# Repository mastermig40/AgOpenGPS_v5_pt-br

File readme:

Este conteúdo é apenas para colaborar com a comunidade AGopenGPS, agradecimentos ao Brian e sua comunidade...

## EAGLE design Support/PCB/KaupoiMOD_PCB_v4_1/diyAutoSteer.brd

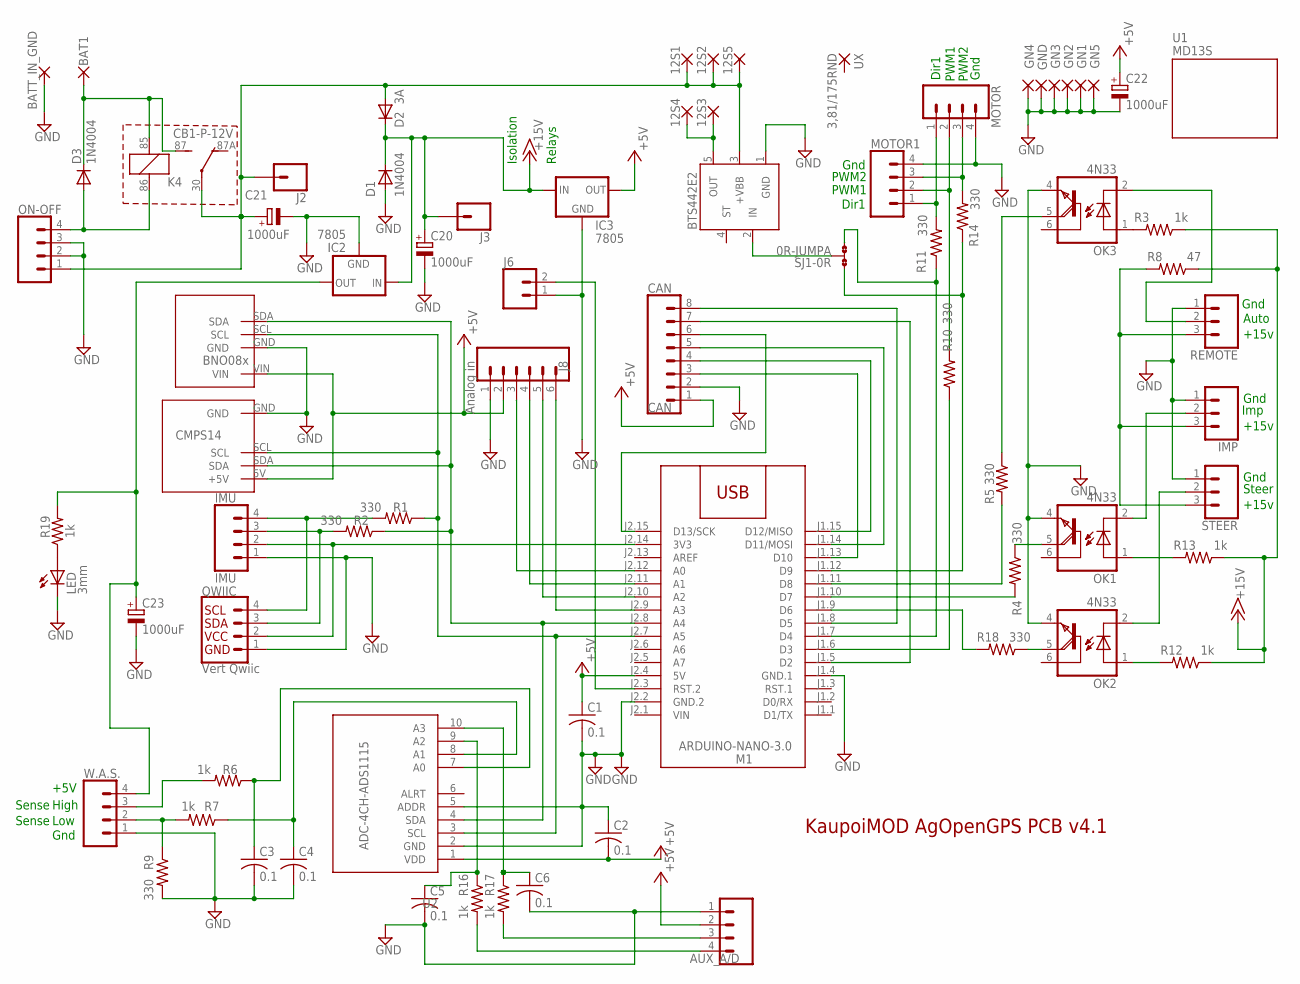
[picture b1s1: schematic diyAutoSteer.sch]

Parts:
12S1, 12S2, 12S3, 12S4, 12S5: 3,81/1,65
AUX_A/D: CONN_04LONGPADS; 1X04_LONGPADS
BAT1: 3,81/1,65
BATT_IN_GND: 3,81/1,65
C1, C2, C3, C4, C5, C6: 0.1; C025-025X050
C20, C21, C22, C23: 1000uF; E5-13
CAN: CAN; 1X08_NO_SILK
D1, D3: 1N4004; DO41-10
D2: 3A; DO27-15
GN1, GN2, GN3, GN4, GN5: 3,81/1,65
GND: 3,81/1,65
IC2, IC3: 7805; 78XXS
IMP: CONN_03LONGPADS; 1X03_LONGPADS
IMU: IMU; 1X04_LONGPADS
J2, J3: CONN_01; 1X01
J6: CONN_02PTH3; 1X02_LONGPADS
J8: Analog in; 1X06_NO_SILK
K4: CB1-P-12V; CB1
LED: 3mm; LED3MM
M1: ARDUINO-NANO-3.0
MOTOR, MOTOR1: CONN_04LONGPADS; 1X04_LONGPADS
OK1, OK2, OK3: 4N33; DIL06
ON-OFF: CONN_04LONGPADS; 1X04_LONGPADS
QWIIC: Vert Qwiic; JST04_1MM_VERT
R1, R2, R4, R5, R9, R10, R11, R14, R18: 330; 0309/12
R3, R6, R7, R12, R13, R16, R17, R19: 1k; 0309/12
R8: 47; 0309/12
REMOTE: CONN_03LONGPADS; 1X03_LONGPADS
SJ1: 0R-JUMPA; A0R-JMP
STEER: CONN_03LONGPADS; 1X03_LONGPADS
U1: MD13S
U2: ADC-4CH-ADS1115
U3: BTS442E2; TO220-5
U4: CMPS14
U5: BNO085
UX: 3,81/175RND; 3,81/1,75RND
W.A.S.: CONN_04LONGPADS; 1X04_LONGPADS

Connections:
+5V: AUX_A/D.2, C1.1, C2.2, C22.+, CAN.1, IC3.OUT, J8.2, M1.J2.4 (5V), U2.1 (VDD), U4.5V (+5V), U5.VIN
+15V: C20.+, D1.C, D2.C, IC2.IN, IC3.IN, J3.1, R3.1, R8.1, R12.1, R13.1
BATT: BAT1.P$1, D3.C, K4.85 (2), K4.87 (S)
DIR: MOTOR.1, MOTOR1.1, R11.2
GND: AUX_A/D.1, BATT_IN_GND.P$1, C1.2, C2.1, C3.2, C4.2, C5.2, C6.2, C20.-, C21.-, C22.-, C23.-, CAN.2, D1.A, GN1.P$1, GN2.P$1, GN3.P$1, GN4.P$1, GN5.P$1, GND.P$1, IC2.GND, IC3.GND, IMP.1, IMU.1, J6.1, J8.1, LED.K (C), M1.J1.4 (GND.1), M1.J2.2 (GND.2), MOTOR.4, MOTOR1.4, OK1.4 (E), OK2.4 (E), OK3.4 (E), ON-OFF.2, ON-OFF.3, QWIIC.1, R9.2, REMOTE.1, STEER.1, U2.2 (GND), U2.5 (ADDR), U3.1 (GND), U4.GND, U5.GND, W.A.S..1
unnamed: IMU.2, M1.J2.14 (3V3), QWIIC.2
unnamed: R7.2, R9.1, W.A.S..2
unnamed: IMP.3, R8.2, REMOTE.3, STEER.3
unnamed: M1.J1.6 (D3), R10.1
unnamed: M1.J1.7 (D4), R11.1, SJ1.3
unnamed: CAN.7, M1.J1.5 (D2)
unnamed: J6.2, M1.J2.3 (RST.2)
unnamed: R6.2, W.A.S..3
unnamed: CAN.8, M1.J1.8 (D5)
unnamed: J8.4, M1.J2.11 (A1)
unnamed: M1.J1.12 (D9), R14.1, SJ1.1
unnamed: IMU.3, QWIIC.3, R2.2
unnamed: IMU.4, QWIIC.4, R1.2
unnamed: J8.5, M1.J2.10 (A2)
unnamed: J8.6, M1.J2.9 (A3)
unnamed: LED.A, R19.1
unnamed: CAN.6, M1.J2.15 (D13/SCK)
unnamed: AUX_A/D.3, R17.2
unnamed: OK1.5 (COL), R4.1
unnamed: C3.1, R6.1, U2.7 (A0)
unnamed: CAN.5, M1.J1.14 (D11/MOSI)
unnamed: OK2.2 (C), STEER.2
unnamed: M1.J1.11 (D8), R5.2
unnamed: D3.A, K4.86 (1), ON-OFF.4
unnamed: OK2.1 (A), R12.2
unnamed: OK3.1 (A), R3.2
unnamed: M1.J1.10 (D7), R4.2
unnamed: OK3.2 (C), REMOTE.2
unnamed: IMP.2, OK1.2 (C)
unnamed: J8.3, M1.J2.12 (A0)
unnamed: M1.J1.9 (D6), R18.2
unnamed: OK1.1 (A), R13.2
unnamed: CAN.4, M1.J1.15 (D12/MISO)
unnamed: OK3.5 (COL), R5.1
unnamed: C6.1, R17.1, U2.10 (A3)
unnamed: C5.1, R16.1, U2.9 (A2)
unnamed: CAN.3, M1.J1.13 (D10)
unnamed: M1.J2.7 (A5), R1.1, U2.3 (SCL), U4.SCL, U5.SCL
unnamed: OK2.5 (COL), R18.1
unnamed: 12S3.P$1, 12S4.P$1, U3.5 (OUT)
unnamed: SJ1.2, U3.2 (IN)
unnamed: C4.1, R7.1, U2.8 (A1)
unnamed: AUX_A/D.4, R16.2
PWM1: MOTOR.2, MOTOR1.2, R10.2
PWM2: MOTOR.3, MOTOR1.3, R14.2
SDA: M1.J2.8 (A4), R2.1, U2.4 (SDA), U4.SDA, U5.SDA
SW_RAW: 12S1.P$1, 12S2.P$1, 12S5.P$1, C21.+, D2.A, J2.1, K4.30, ON-OFF.1, U3.3 (+VBB)
V+WAS: C23.+, IC2.OUT, R19.2, W.A.S..4
VIN: M1.J2.1 (VIN)

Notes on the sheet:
Gnd
Low
High
+5V
PWM1
PWM2
Dir1
Steer
Imp
Sense
Auto
Isolation
Relays
+15v
KaupoiMOD AgOpenGPS PCB v4.1

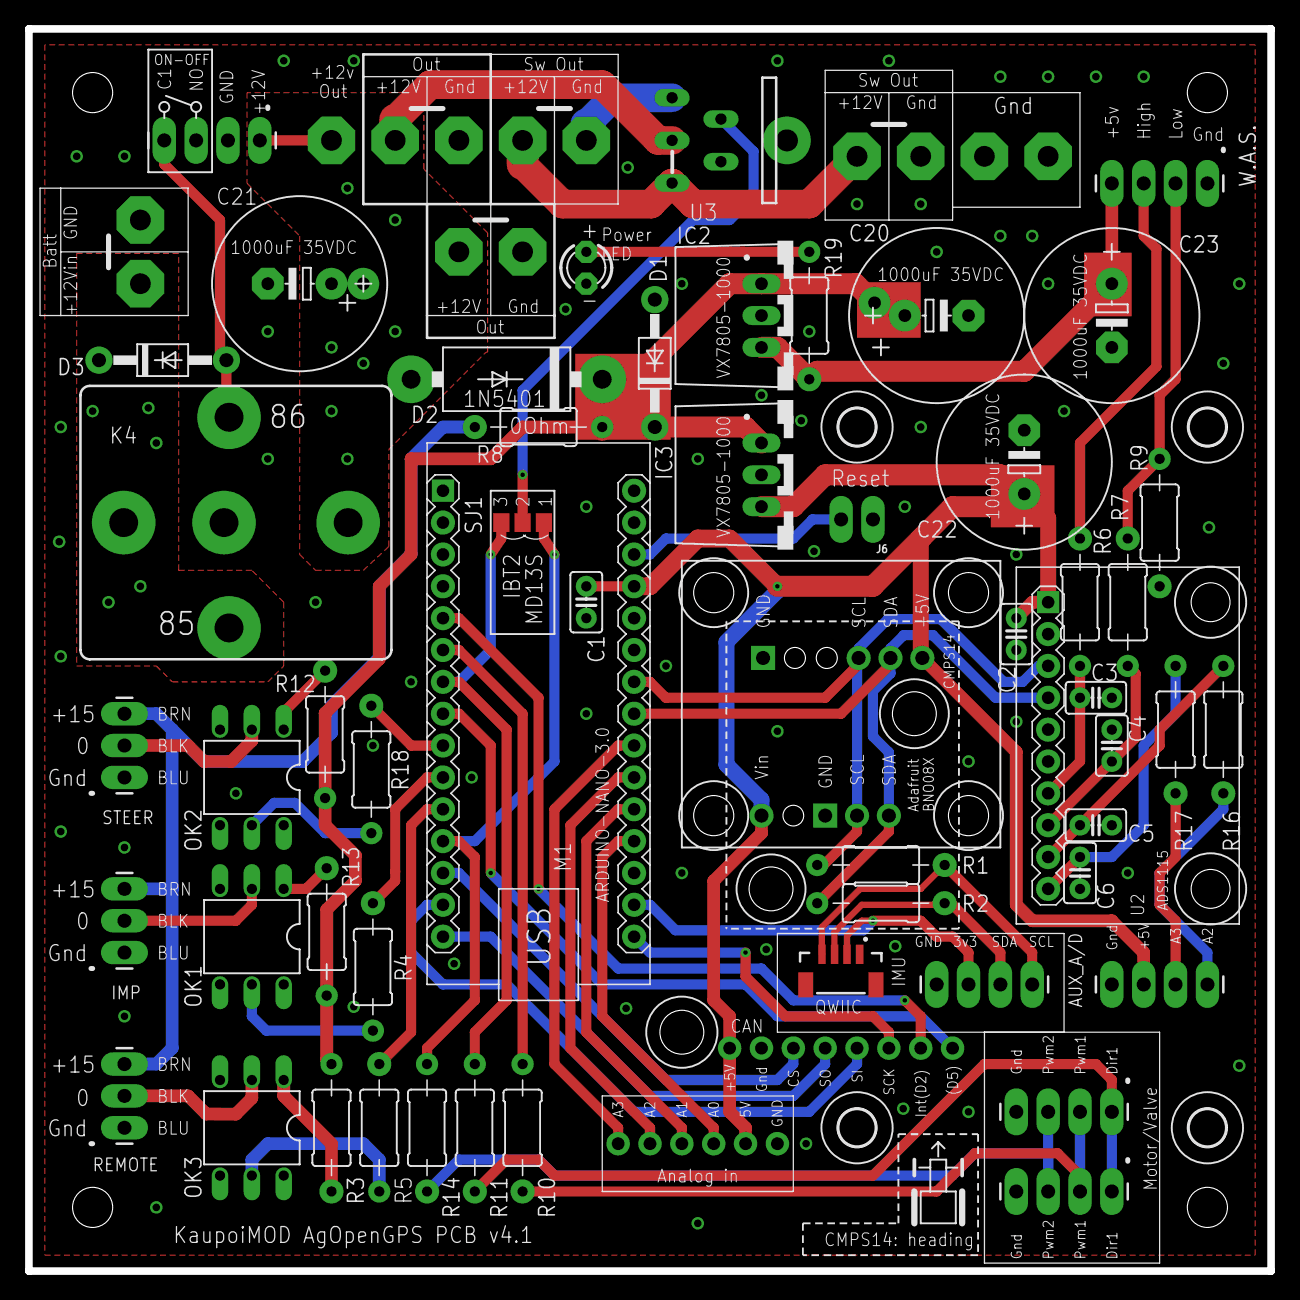
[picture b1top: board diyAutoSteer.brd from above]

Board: 2 copper layers, 99.1 x 99.1 mm, 74 parts (0 on the bottom side), 53 nets.

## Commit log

2023-05-29 Atualização 29-05-23
    enviando arquivos

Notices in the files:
parts and their libraries:
SparkFun-Connectors: Licensing: Creative Commons ShareAlike 4.0 International - https://creativecommons.org/licenses/by-sa/4.0
diy-modules: Released under the Creative Commons Attribution 4.0 International License: http://creativecommons.org/licenses/by/4.0
